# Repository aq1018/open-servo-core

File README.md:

# open-servo-core

Democratize Robotics For Everyone

## Overview

This project aims to create a drop-in replacement control board for MG90-class servos that adds cascade control, current sensing, and a DYNAMIXEL-style serial protocol. The goal is to make robotics more accessible by turning a $2.50 servo into a $5 smart actuator (vs $30+ for commercial alternatives). Built with bare-metal Rust on CH32V microcontrollers.

## Project Status

🚧 **Early Development** - Not ready for general use

- ✅ **Working**: Basic PID control, PWM motor drive, current sensing, ADC readings
- 🔄 **In Progress**: Cascade control loops, UART protocol implementation  
- 📋 **Planned**: System identification, auto-tuning, multi-servo bus communication

## Project Structure

```
firmware/open-servo-core/  - Rust firmware for CH32V
hardware/
  servo-dev-board/         - Development board for firmware testing  
  encoder-board/           - Quadrature IR sensor board for system ID
  motor-mount/             - Test fixtures and mechanical designs
  common/                  - Shared KiCad symbols & footprints
```

## Development

- **Firmware**: Bare-metal Rust using PAC-level drivers, debugged with probe-rs and defmt
- **Hardware**: KiCad designs with JLCPCB production files available
- **Target MCU**: CH32V003 (RISC-V, ultra low-cost)
- **Control**: Cascaded loops - current → velocity → position

## Goals

- Implement cascade control with inner current, middle velocity, and outer position loops
- Create a DYNAMIXEL-inspired protocol for controlling multiple servos on one bus
- Add system identification and auto-tuning capabilities
- Keep total cost under $5 per modified servo
- Require no mechanical modifications to the servo

## Contributing

This is experimental research code in active development. Issues and discussions are welcome. Check the hardware folders for KiCad designs and the firmware folder for the Rust implementation.

## License

MIT License - See [LICENSE](LICENSE) file for details

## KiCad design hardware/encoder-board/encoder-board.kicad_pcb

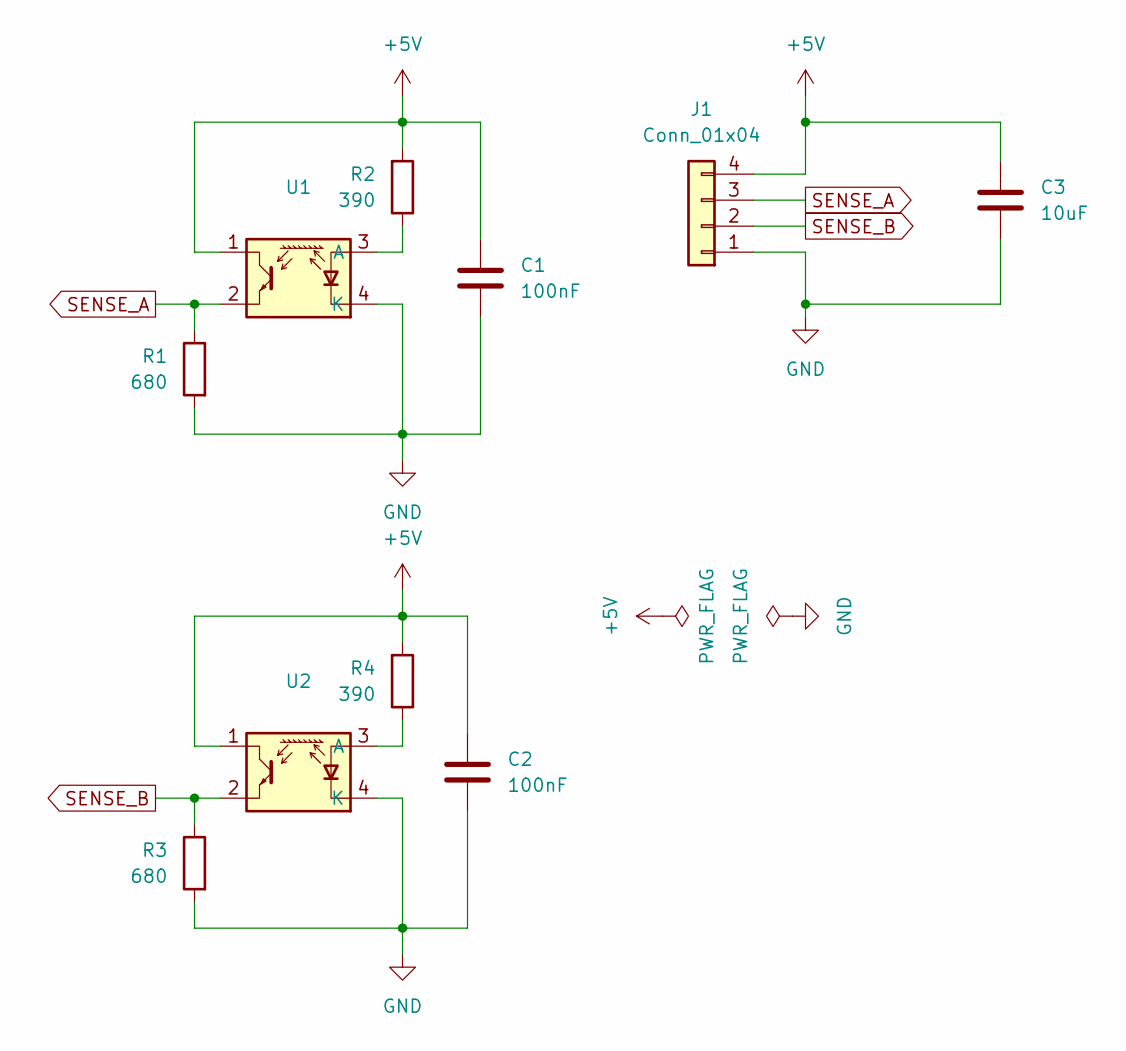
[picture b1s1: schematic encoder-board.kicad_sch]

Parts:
C1, C2: 100nF; C_0805_2012Metric_Pad1.18x1.45mm_HandSolder
C3: 10uF; C_0805_2012Metric_Pad1.18x1.45mm_HandSolder
J1: Conn_01x04; PinHeader_1x04_P2.54mm_Vertical; LCSC C780062
R1, R3: 680; R_0805_2012Metric_Pad1.20x1.40mm_HandSolder; LCSC C22548
R2, R4: 390; R_0805_2012Metric_Pad1.20x1.40mm_HandSolder; LCSC C125923
U1, U2: ITR1204SR10A_TR(BY); OPTO-SMD-4_ITR1204SR10A; LCSC C475373

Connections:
+5V: C1.1, C2.1, C3.1, J1.4, R2.2, R4.2, U1.1, U2.1
GND: C1.2, C2.2, C3.2, J1.1, R1.2, R3.2, U1.4 (K), U2.4 (K)
unnamed: R2.1, U1.3 (A)
unnamed: R4.1, U2.3 (A)
SENSE_A: J1.3, R1.1, U1.2
SENSE_B: J1.2, R3.1, U2.2

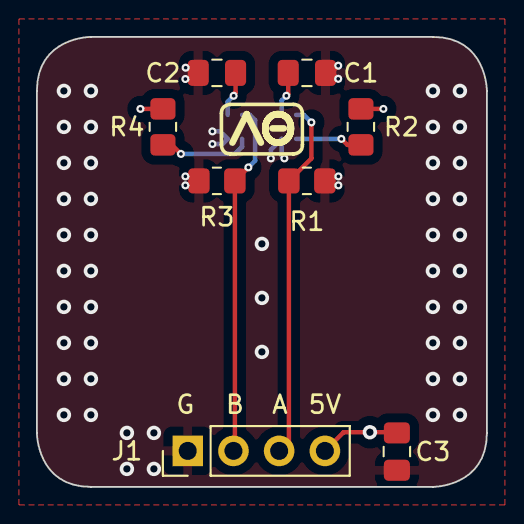
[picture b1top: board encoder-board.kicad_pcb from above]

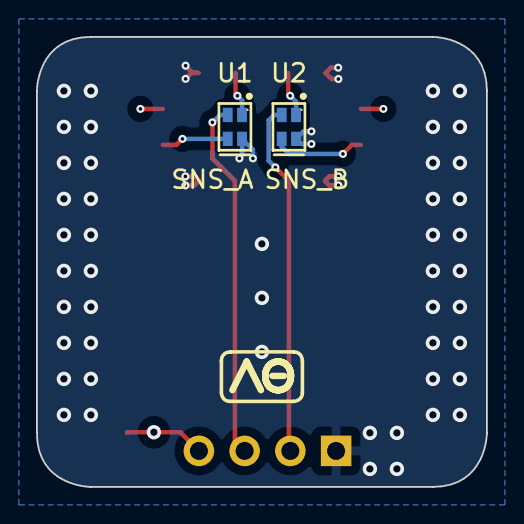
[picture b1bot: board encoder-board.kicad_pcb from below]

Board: 4 copper layers, 25.0 x 25.0 mm, 10 parts (2 on the bottom side), 6 nets.

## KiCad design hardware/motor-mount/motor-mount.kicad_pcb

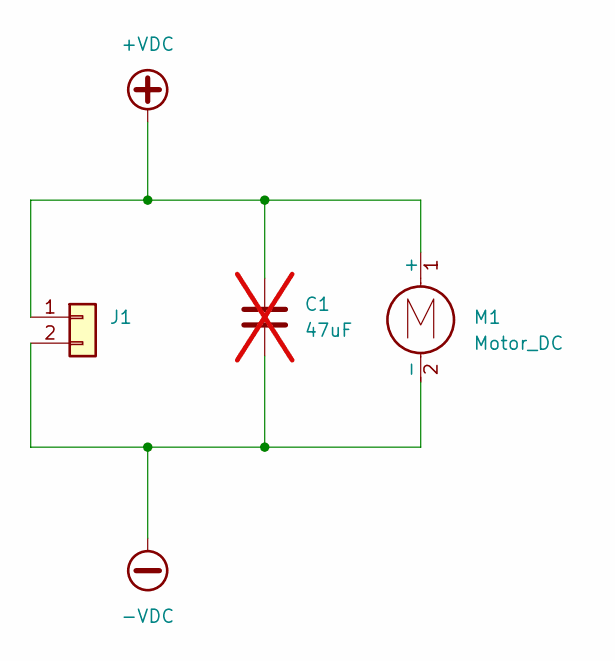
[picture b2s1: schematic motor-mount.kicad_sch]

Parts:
C1: 47uF; C_1206_3216Metric; not fitted
J1: PinHeader_1x02_P2.54mm_Vertical
M1: Motor_DC; SG90_Motor

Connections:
+VDC: C1.1, J1.1, M1.1 (+)
-VDC: C1.2, J1.2, M1.2 (-)

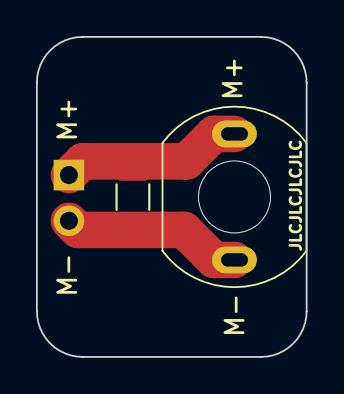
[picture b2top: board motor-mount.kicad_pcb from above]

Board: 2 copper layers, 15.0 x 17.8 mm, 3 parts (1 on the bottom side), 2 nets.

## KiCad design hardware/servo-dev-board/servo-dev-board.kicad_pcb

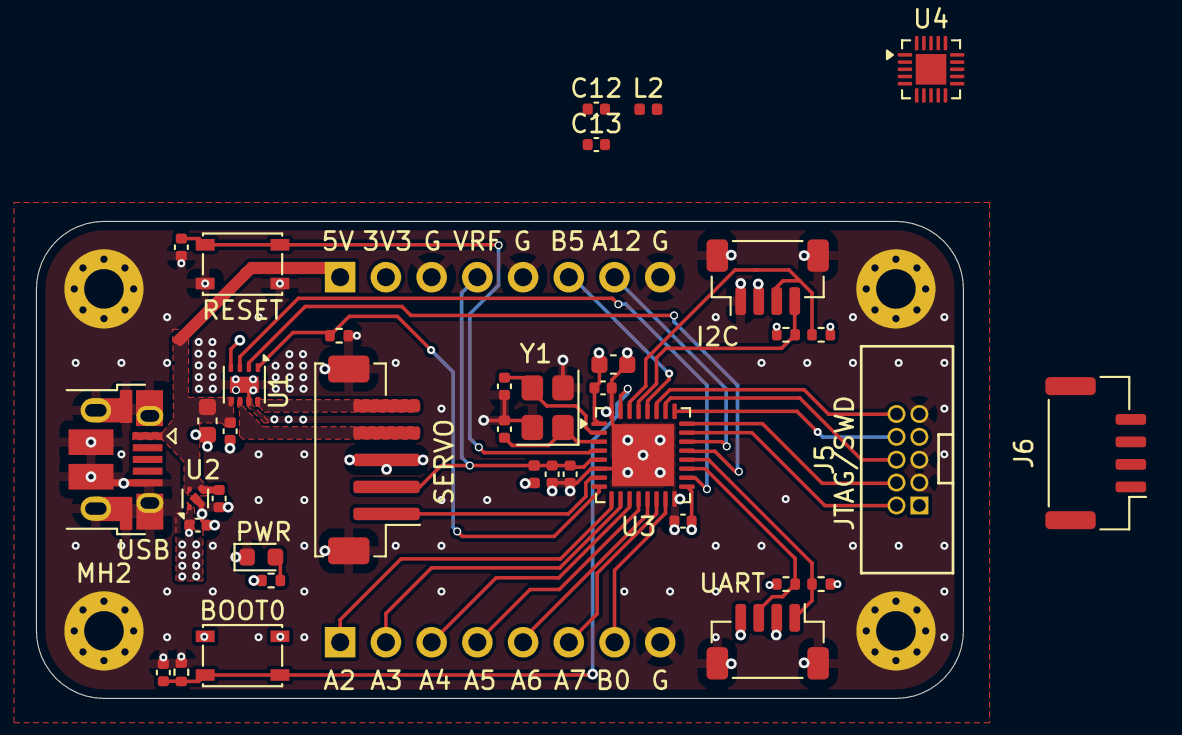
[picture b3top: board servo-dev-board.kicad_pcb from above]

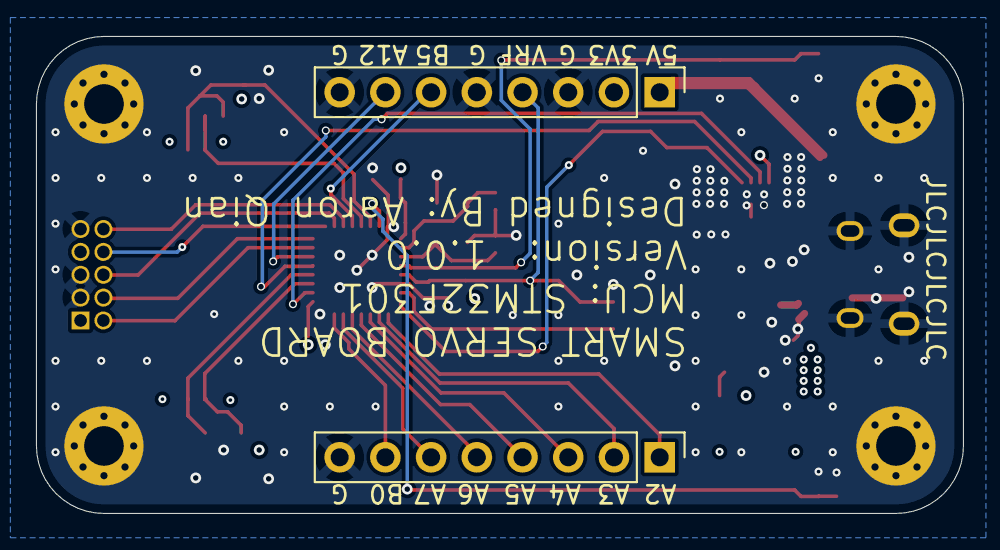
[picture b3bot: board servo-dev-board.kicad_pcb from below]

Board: 4 copper layers, 51.5 x 26.5 mm, 44 parts (2 on the bottom side), 34 nets.

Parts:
C1, C2, C3, C6, C7, C13: 0.1uF; C_0402_1005Metric
C4, C5, C10: 1uF; C_0402_1005Metric
C8: 4.7uF; C_0603_1608Metric
C9: 10nF; C_0402_1005Metric
C11: 22uF; C_0603_1608Metric
C12: 10uF; C_0402_1005Metric
CL1, CL2: 12pF; C_0402_1005Metric
H1, H2: Conn_01x08_Pin; PinHeader_1x08_P2.54mm_Vertical
J1: USB_B_Micro; USB_Micro-B_Amphenol_10103594-0001LF_Horizontal
J2: Conn_01x05_MountingPin; JST_ZH_B5B-ZR-SM4-TF_1x05-1MP_P1.50mm_Vertical
J3, J4: Conn_01x04_MountingPin; JST_SH_BM04B-SRSS-TB_1x04-1MP_P1.00mm_Vertical
J5: Conn_02x05_Odd_Even; IDC-TH_10P-P1.27-X1270WV-2X05A-6TV01
J6: Conn_01x04_MountingPin; JST_GH_BM04B-GHS-TBT_1x04-1MP_P1.25mm_Vertical
L1, L2: 1kΩ@100Mhz; L_0402_1005Metric
LED1: RED; LED_0603_1608Metric
MH1, MH2, MH3, MH4: MountingHole_Pad_MP; MountingHole_2.2mm_M2_Pad_Via
R1, R2, R3, R4, R5, R6: 4K7; R_0402_1005Metric
R7: 1K5; R_0402_1005Metric
SW1, SW2: SW_Push; SW_SPST_PTS810
U1: DRV8231ADSGR; WSON-8-1EP_2x2mm_P0.5mm_EP0.9x1.6mm
U2: SSP7615-33DFR; UDFN-4-1EP_1x1mm_P0.65mm_EP0.48x0.48mm
U3: STM32F301K8Ux; QFN-32-1EP_5x5mm_P0.5mm_EP3.45x3.45mm
U4: CH32V006F8U6; UQFN-20-1EP_3x3mm_P0.4mm_EP1.7x1.7mm
Y1: 16MHz 9pF; Crystal_SMD_3225-4Pin_3.2x2.5mm

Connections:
+3V3: C4.2, C6.2, C7.2, C8.2, H2.2, J3.2, J4.4, J5.1, L1.2, R1.2, R2.1, R3.1, R4.2, R5.1, SW2.1, U1.4 (VREF), U2.1 (VOUT), U3.1 (VDD), U3.17 (VDD)
+5V: C1.2, C5.2, C11.2, C12.2, H2.1, J1.1 (VBUS), J6.1, L2.1, U1.5 (VM), U2.3 (EN), U2.4 (VIN)
/+5V_TRX: C13.2, L2.2
/BOOT0: C3.1, R6.1, SW2.2, U3.31 (BOOT0)
/I2C1_SCL: J3.4, R3.2, U3.29 (PB6)
/I2C1_SDA: J3.3, R2.2, U3.30 (PB7)
/ISNS: R7.1, U1.1 (IPROPI), U3.8 (PA1)
/JTCK_SWCLK: J5.4, U3.24 (PA14)
/JTDI: J5.8, U3.25 (PA15)
/JTDO_SWO: J5.6, U3.26 (PB3)
/JTMS_SWDIO: J5.2, U3.23 (PA13)
/M1: J2.4, U1.6 (OUT1)
/M2: J2.5, U1.8 (OUT2)
/NJTRST: J5.10, U3.27 (PB4)
/NRST: C2.2, SW1.1, U3.4 (NRST), U4.1 (PD7/RST/T2C4/OPP1/PA4/U2TX_/OPN2)
/OSC+: CL1.1, U3.3 (PF1), Y1.1
/OSC-: CL2.2, U3.2 (PF0), Y1.3
/PA2: H1.1, U3.9 (PA2)
/PA3: H1.2, U3.10 (PA3)
/PA4: H1.3, U3.11 (PA4)
/PA5: H1.4, U3.12 (PA5)
/PA6: H1.5, U3.13 (PA6)
/PA7: H1.6, U3.14 (PA7)
/PA12: H2.7, U3.22 (PA12)
/PB0: H1.7, U3.15 (PB0)
/PB5: H2.6, U3.28 (PB5)
/POT: J2.1, U3.7 (PA0), U4.17 (PD3/T1/T2/U2RX_/NSS_/OPP2/A4)
/PWM1: U1.3 (IN1), U3.18 (PA8)
/PWM2: U1.2 (IN2), U3.21 (PA11)
/UART1_RX: J4.1, R1.1, U3.20 (PA10), U4.20 (PD6/T2/RX/TX_/MOSI_/A6)
/UART1_TX: J4.3, R4.1, U3.19 (PA9), U4.19 (PD5/T2/TX/RX_/MISO_/A5)
/VREF: C9.2, C10.2, H2.4, J2.2, L1.1, U3.5 (VDDA)
GND: C1.1, C2.1, C3.2, C4.1, C5.1, C6.1, C7.1, C8.1, C9.1, C10.1, C11.1, C12.1, C13.1, CL1.2, CL2.1, H1.8, H2.3, H2.5, H2.8, J1.5 (GND), J1.6 (Shield), J2.3, J2.MP (MountPin), J3.1, J3.MP (MountPin), J4.2, J4.MP (MountPin), J5.3, J5.5, J5.9, J6.2, LED1.1 (K), R6.2, R7.2, SW1.2, U1.7 (GND), U1.9 (EP), U2.2 (GND), U2.5 (EP), U3.6 (VSSA), U3.16 (VSS), U3.32 (VSS), U3.33 (VSS), U4.4 (VSS), U4.21 (VSS), Y1.2, Y1.4
unnamed: LED1.2 (A), R5.2

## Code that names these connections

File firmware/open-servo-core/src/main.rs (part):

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fn TIM2() {
    defmt::info!("TIM2 interrupt");

    // toggle PA3
    unsafe {
        (*pac::GPIOA::ptr())
            .odr
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    /*
     * Configure ADC Channels
     */
    // configure PA0, PA1, PA2 as analog input
    let gpioa = &p.GPIOA;
    gpioa
        .moder
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            .sq1()
            .bits(18) // set vrefint ( ch 18 ) as first conversion
            .sq2()
            .bits(1) // set PA0 ( ch 1 )  as second conversion
            .sq3()
            .bits(2) // set PA1 ( ch 2 )  as third conversion
            .sq4()
            .bits(3) // set PA2 ( ch 3 ) as fourth conversion
    });

    adc1.sqr2.modify(|_, w| unsafe {
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    // set sample time for channels
    adc1.smpr1.modify(|_, w| {
        w.smp1()
            .cycles181_5() // PA0
            .smp2()
            .cycles181_5() // PA1
            .smp3()
            .cycles181_5() // PA2
    });

    adc1.smpr2.modify(|_, w| {
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fn init_led(p: &pac::Peripherals) {
    let gpioa = &p.GPIOA;

    // configure PA3 as output
    gpioa.moder.modify(|_, w| w.moder3().output());

    // configure PA3 as push-pull
    gpioa.otyper.modify(|_, w| w.ot3().push_pull());

    // configure PA3 as high speed output
    gpioa.ospeedr.modify(|_, w| w.ospeedr3().high_speed());

    // configure PA3 as no pull-up, no pull-down
    gpioa.pupdr.modify(|_, w| w.pupdr3().floating());

    // set PA3 to low
    gpioa.odr.modify(|_, w| w.odr3().low());
}

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    let gpioa = &p.GPIOA;
    let tim1 = &p.TIM1;

    // configure PA8 ( channel 1 ) as PWM output
    {
        // configure PA8 as alternate function
        gpioa.moder.modify(|_, w| w.moder8().alternate());

        // set PA8 alternate function map to TIM1_CH1 ( AF6 )
        gpioa.afrh.modify(|_, w| w.afrh8().af6());

        // configure PA8 as high speed output
        gpioa.ospeedr.modify(|_, w| w.ospeedr8().high_speed());

        // configure PA8 as push-pull
        gpioa.otyper.modify(|_, w| w.ot8().push_pull());

        // configure PA8 as pull down
        gpioa.pupdr.modify(|_, w| w.pupdr8().pull_down());

        // configure Channel 1 as PWM mode 1 and enable preload register
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        tim1.ccer.modify(|_, w| w.cc3e().set_bit());
    }

    // configure PA11 ( channel 4 ) as PWM output
    {
        // configure PA11 as alternate function
        gpioa.moder.modify(|_, w| w.moder11().alternate());

        // set PA11 alternate function map to TIM1_CH4 ( AF11 )
        gpioa.afrh.modify(|_, w| w.afrh11().af11());

        // configure PA11 as high speed output
        gpioa.ospeedr.modify(|_, w| w.ospeedr11().high_speed());

        // configure PA11 as push-pull
        gpioa.otyper.modify(|_, w| w.ot11().push_pull());

        // configure PA11 as pull down
        gpioa.pupdr.modify(|_, w| w.pupdr11().pull_down());

        // configure TIM1 as PWM mode 1 and enable preload register
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
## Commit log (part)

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2025-11-02 fix encoder schematics. Prepare to redo pcb.
2025-11-02 refine encoder disk. Add reflective bars to encoder
2025-11-27 simplify encoder board to output analog output
2025-11-27 overhaul servo dev board to use ch32v00X
2025-11-27 remake encoder board pcb. generated jlcpcb production files.
2025-11-27 fix sensor chip 3d rendering
2025-11-28 fix encoder board references
